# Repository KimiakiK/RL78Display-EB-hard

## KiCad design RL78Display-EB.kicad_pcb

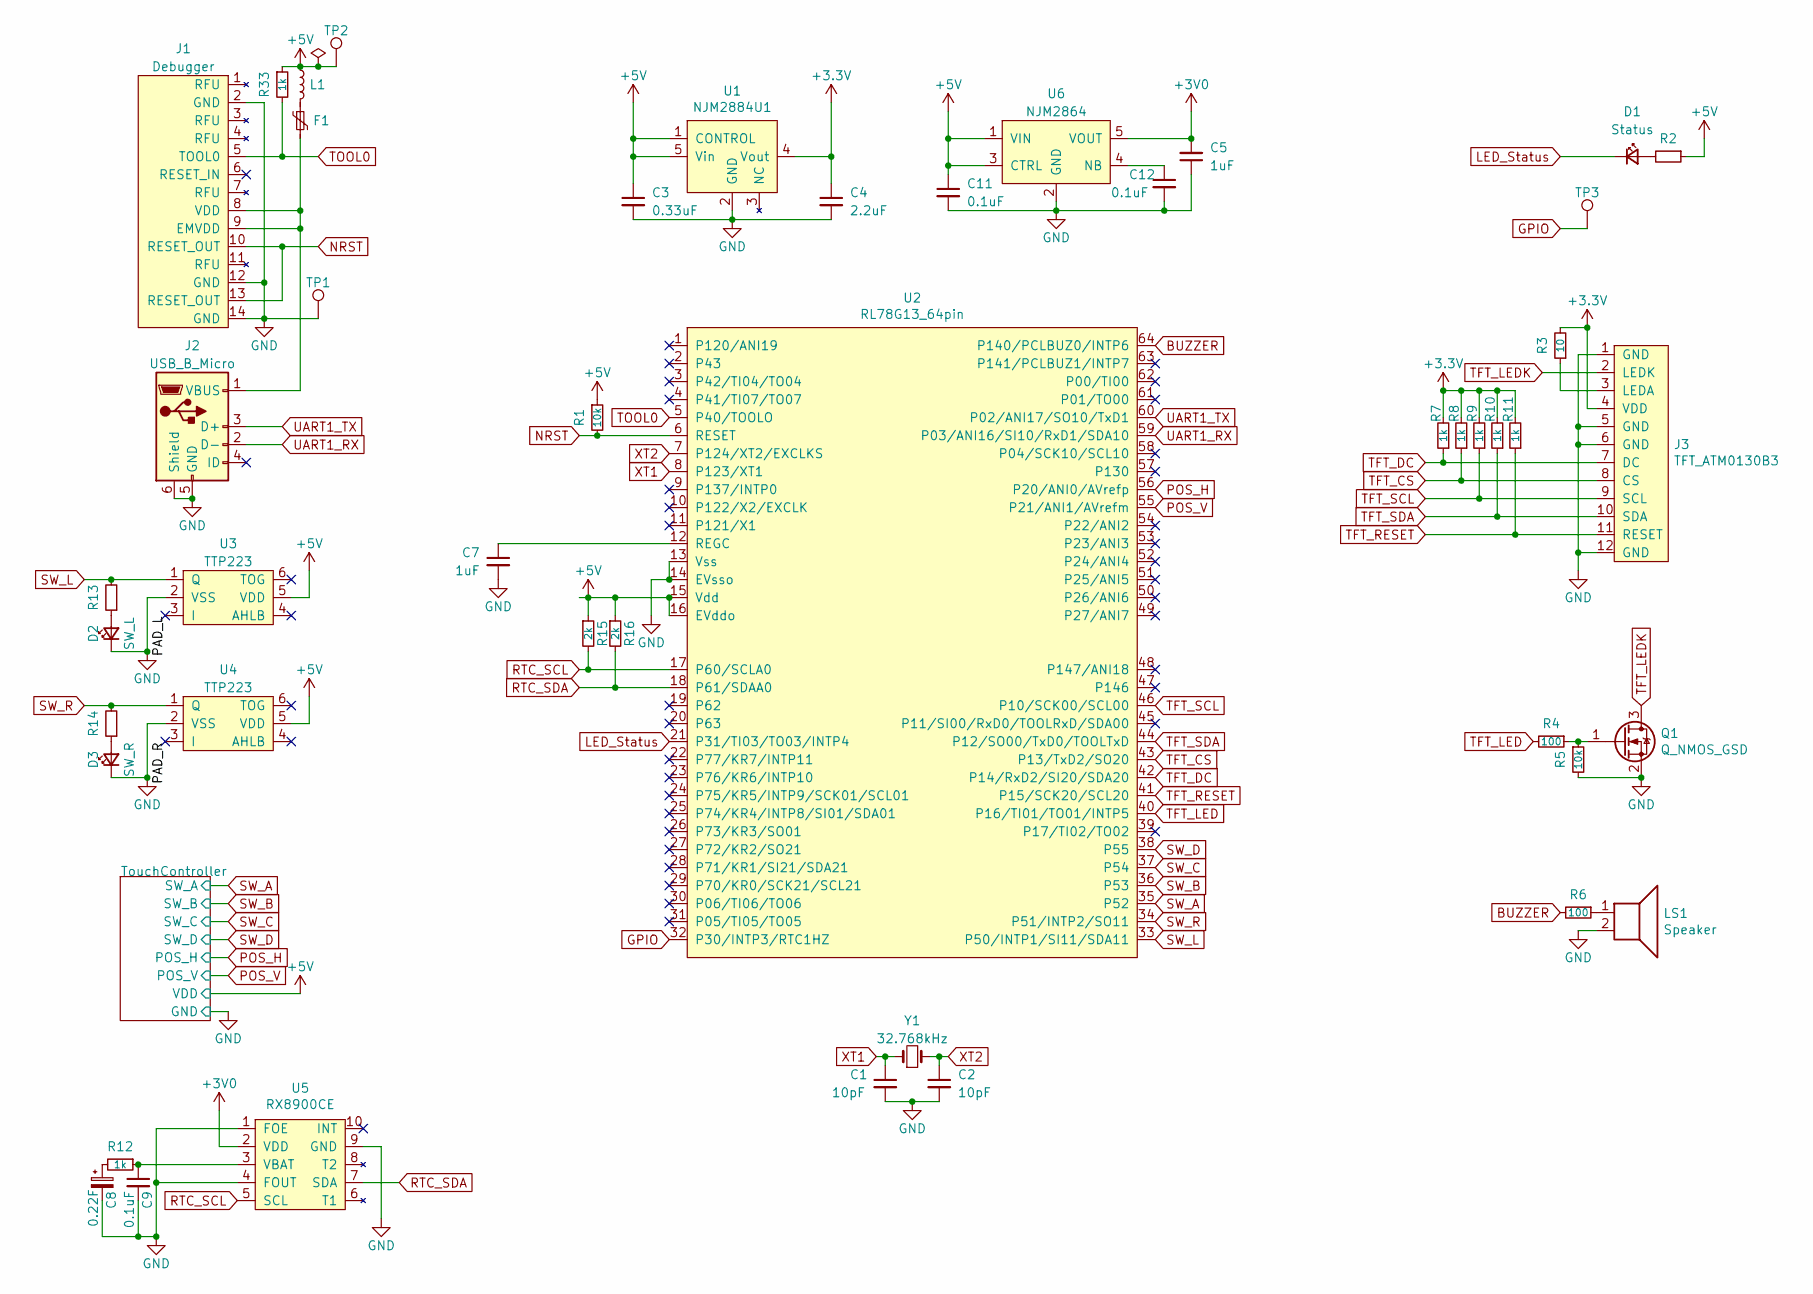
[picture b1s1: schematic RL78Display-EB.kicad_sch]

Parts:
C1, C2: 10pF; 1005Metric
C3: 0.33uF; 1608Metric
C4: 2.2uF; 1608Metric
C5, C7: 1uF; 1608Metric
C8: 0.22F; DCK-3R3E224-E
C9, C11, C12: 0.1uF; 1608Metric
D1: Status; 1608Metric
D2: SW_L; 1608Metric
D3: SW_R; 1608Metric
F1: Polyfuse_Small; 1608Metric
J1: Debugger; IDC-Header_2x07_P2.54mm_Vertical
J2: USB_B_Micro; UX60SC-MB-5ST
J3: TFT_ATM0130B3; Hirose_FH12-12S-0.5SH_1x12-1MP_P0.50mm_Horizontal
L1: L_Small; 1608Metric
LS1: Speaker; PKMCS0909E4000
Q1: Q_NMOS_GSD; SOT-23
R1, R5: 10k; 1608Metric
R2, R13, R14: R; 1608Metric
R3: 10; 1608Metric
R4, R6: 100; 1608Metric
R7, R8, R9, R10, R11, R12, R33: 1k; 1608Metric
R15, R16: 2k; 1608Metric
TP1, TP2, TP3: TestPoint; TestPoint_THTPad_D1.4mm_Drill0.8mm
U1: NJM2884U1; SOT-89-5
U2: RL78G13_64pin; LQFP-64-12x12mm-P0.65mm_FusionPCB_TP
U3, U4: TTP223; SOT-23-6
U5: RX8900CE
U6: NJM2864; SOT-23-5
Y1: 32.768kHz; Crystal_SMD_3215-2Pin

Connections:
+3.3V: C4.1, J3.4 (VDD), R3.2, R7.2, R8.2, R9.2, R10.2, R11.2, U1.4 (Vout)
+3V0: C5.2, U5.2 (VDD), U6.5 (VOUT)
+5V: C3.1, C11.1, L1.1, R1.1, R2.1, R15.1, R16.1, R33.1, TP2.1, U1.1 (CONTROL), U1.5 (Vin), U2.15 (Vdd), U2.16 (EVddo), U3.5 (VDD), U4.5 (VDD), U6.1 (VIN), U6.3 (CTRL); also elsewhere on the board
/PAD_L: U3.3 (I)
/PAD_R: U4.3 (I)
BUZZER: R6.2, U2.64 (P140/PCLBUZ0/INTP6)
GND: C1.2, C2.2, C3.2, C4.2, C5.1, C7.2, C8.2, C9.2, C11.2, C12.2, D2.1 (K), D3.1 (K), J1.2 (GND), J1.12 (GND), J1.14 (GND), J2.5 (GND), J2.6 (Shield), J3.1 (GND), J3.5 (GND), J3.6 (GND), J3.12 (GND), LS1.2, Q1.2 (S), R5.2, TP1.1, U1.2 (GND), U2.13 (Vss), U2.14 (EVsso), U3.2 (VSS), U4.2 (VSS), U5.1 (FOE), U5.4 (FOUT), U5.9 (GND), U6.2 (GND); also elsewhere on the board
GPIO: TP3.1, U2.32 (P30/INTP3/RTC1HZ)
LED_Status: D1.1 (K), U2.21 (P31/TI03/TO03/INTP4)
NRST: J1.10 (RESET_OUT), J1.13 (RESET_OUT), R1.2, U2.6 (RESET)
unnamed: C7.1, U2.12 (REGC)
unnamed: C8.1, R12.2
unnamed: C9.1, R12.1, U5.3 (VBAT)
unnamed: C12.1, U6.4 (NB)
unnamed: D1.2 (A), R2.2
unnamed: D2.2 (A), R13.1
unnamed: D3.2 (A), R14.1
unnamed: F1.1, L1.2
unnamed: F1.2, J1.8 (VDD), J1.9 (EMVDD), J2.1 (VBUS)
unnamed: J3.3 (LEDA), R3.1
unnamed: LS1.1, R6.1
unnamed: Q1.1 (G), R4.1, R5.1
POS_H: U2.56 (P20/ANI0/AVrefp); also elsewhere on the board
POS_V: U2.55 (P21/ANI1/AVrefm); also elsewhere on the board
RTC_SCL: R15.2, U2.17 (P60/SCLA0), U5.5 (SCL)
RTC_SDA: R16.2, U2.18 (P61/SDAA0), U5.7 (SDA)
SW_A: U2.35 (P52); also elsewhere on the board
SW_B: U2.36 (P53); also elsewhere on the board
SW_C: U2.37 (P54); also elsewhere on the board
SW_D: U2.38 (P55); also elsewhere on the board
SW_L: R13.2, U2.33 (P50/INTP1/SI11/SDA11), U3.1 (Q)
SW_R: R14.2, U2.34 (P51/INTP2/SO11), U4.1 (Q)
TFT_CS: J3.8 (CS), R8.1, U2.43 (P13/TxD2/SO20)
TFT_DC: J3.7 (DC), R7.1, U2.42 (P14/RxD2/SI20/SDA20)
TFT_LED: R4.2, U2.40 (P16/TI01/TO01/INTP5)
TFT_LEDK: J3.2 (LEDK), Q1.3 (D)
TFT_RESET: J3.11 (RESET), R11.1, U2.41 (P15/SCK20/SCL20)
TFT_SCL: J3.9 (SCL), R9.1, U2.46 (P10/SCK00/SCL00)
TFT_SDA: J3.10 (SDA), R10.1, U2.44 (P12/SO00/TxD0/TOOLTxD)
TOOL0: J1.5 (TOOL0), R33.2, U2.5 (P40/TOOLO)
UART1_RX: J2.2 (D-), U2.59 (P03/ANI16/SI10/RxD1/SDA10)
UART1_TX: J2.3 (D+), U2.60 (P02/ANI17/SO10/TxD1)
XT1: C1.1, U2.8 (P123/XT1), Y1.1
XT2: C2.1, U2.7 (P124/XT2/EXCLKS), Y1.2

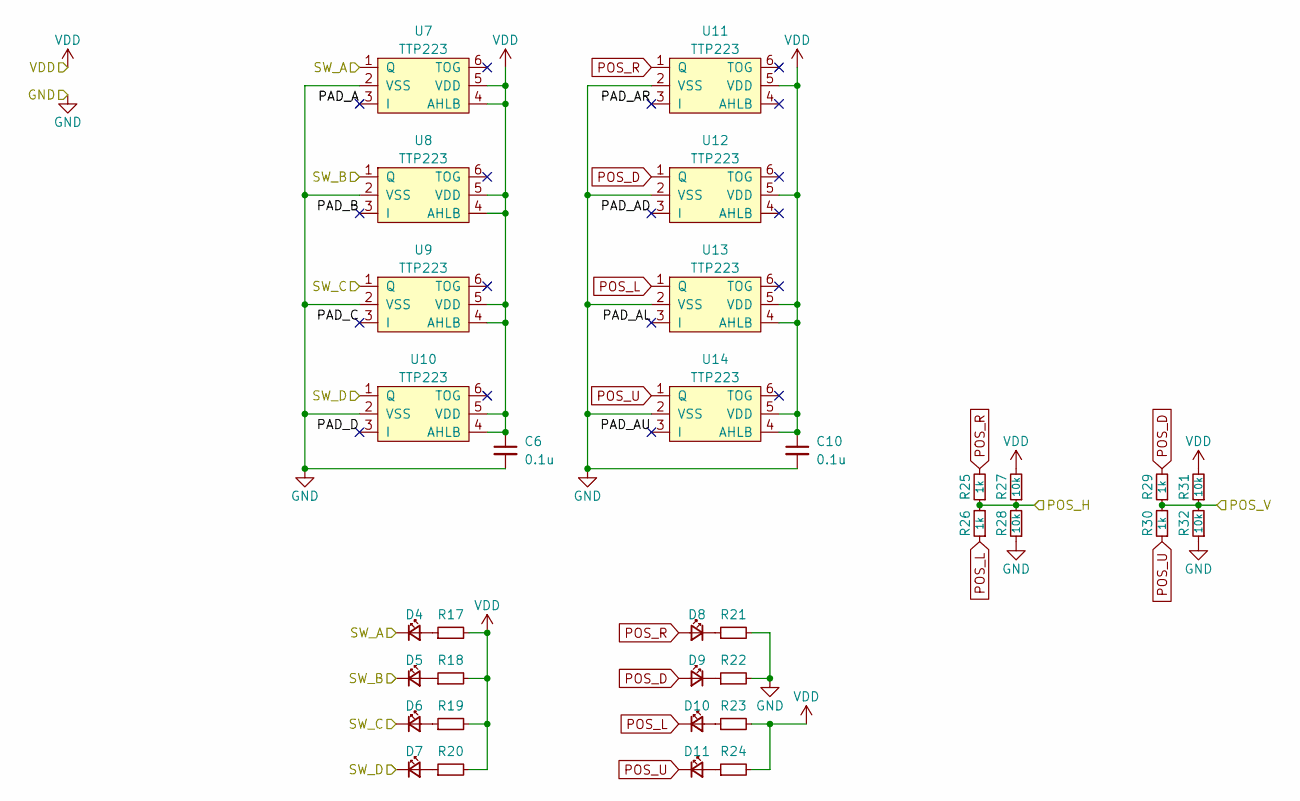
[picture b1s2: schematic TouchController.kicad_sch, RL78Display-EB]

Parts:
C6, C10: 0.1u; 1608Metric
D4, D5, D6, D7, D8, D9, D10, D11: LED; 1608Metric
R17, R18, R19, R20, R21, R22, R23, R24: R; 1608Metric
R25, R26, R29, R30: 1k; 1608Metric
R27, R28, R31, R32: 10k; 1608Metric
U7, U8, U9, U10, U11, U12, U13, U14: TTP223; SOT-23-6

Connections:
+5V: C6.1, C10.1, R17.2, R18.2, R19.2, R20.2, R23.2, R24.2, R27.2, R31.2, U7.4 (AHLB), U7.5 (VDD), U8.4 (AHLB), U8.5 (VDD), U9.4 (AHLB), U9.5 (VDD), U10.4 (AHLB), U10.5 (VDD), U11.5 (VDD), U12.5 (VDD), U13.4 (AHLB), U13.5 (VDD), U14.4 (AHLB), U14.5 (VDD); also elsewhere on the board
/TouchController/PAD_A: U7.3 (I)
/TouchController/PAD_AD: U12.3 (I)
/TouchController/PAD_AL: U13.3 (I)
/TouchController/PAD_AR: U11.3 (I)
/TouchController/PAD_AU: U14.3 (I)
/TouchController/PAD_B: U8.3 (I)
/TouchController/PAD_C: U9.3 (I)
/TouchController/PAD_D: U10.3 (I)
GND: C6.2, C10.2, R21.2, R22.2, R28.1, R32.1, U7.2 (VSS), U8.2 (VSS), U9.2 (VSS), U10.2 (VSS), U11.2 (VSS), U12.2 (VSS), U13.2 (VSS), U14.2 (VSS); also elsewhere on the board
unnamed: D4.2 (A), R17.1
unnamed: D5.2 (A), R18.1
unnamed: D6.2 (A), R19.1
unnamed: D7.2 (A), R20.1
unnamed: D8.1 (K), R21.1
unnamed: D9.1 (K), R22.1
unnamed: D10.2 (A), R23.1
unnamed: D11.2 (A), R24.1
POS_D: D9.2 (A), R29.2, U12.1 (Q)
POS_H: R25.1, R26.2, R27.1, R28.2; also elsewhere on the board
POS_L: D10.1 (K), R26.1, U13.1 (Q)
POS_R: D8.2 (A), R25.2, U11.1 (Q)
POS_U: D11.1 (K), R30.1, U14.1 (Q)
POS_V: R29.1, R30.2, R31.1, R32.2; also elsewhere on the board
SW_A: D4.1 (K), U7.1 (Q); also elsewhere on the board
SW_B: D5.1 (K), U8.1 (Q); also elsewhere on the board
SW_C: D6.1 (K), U9.1 (Q); also elsewhere on the board
SW_D: D7.1 (K), U10.1 (Q); also elsewhere on the board

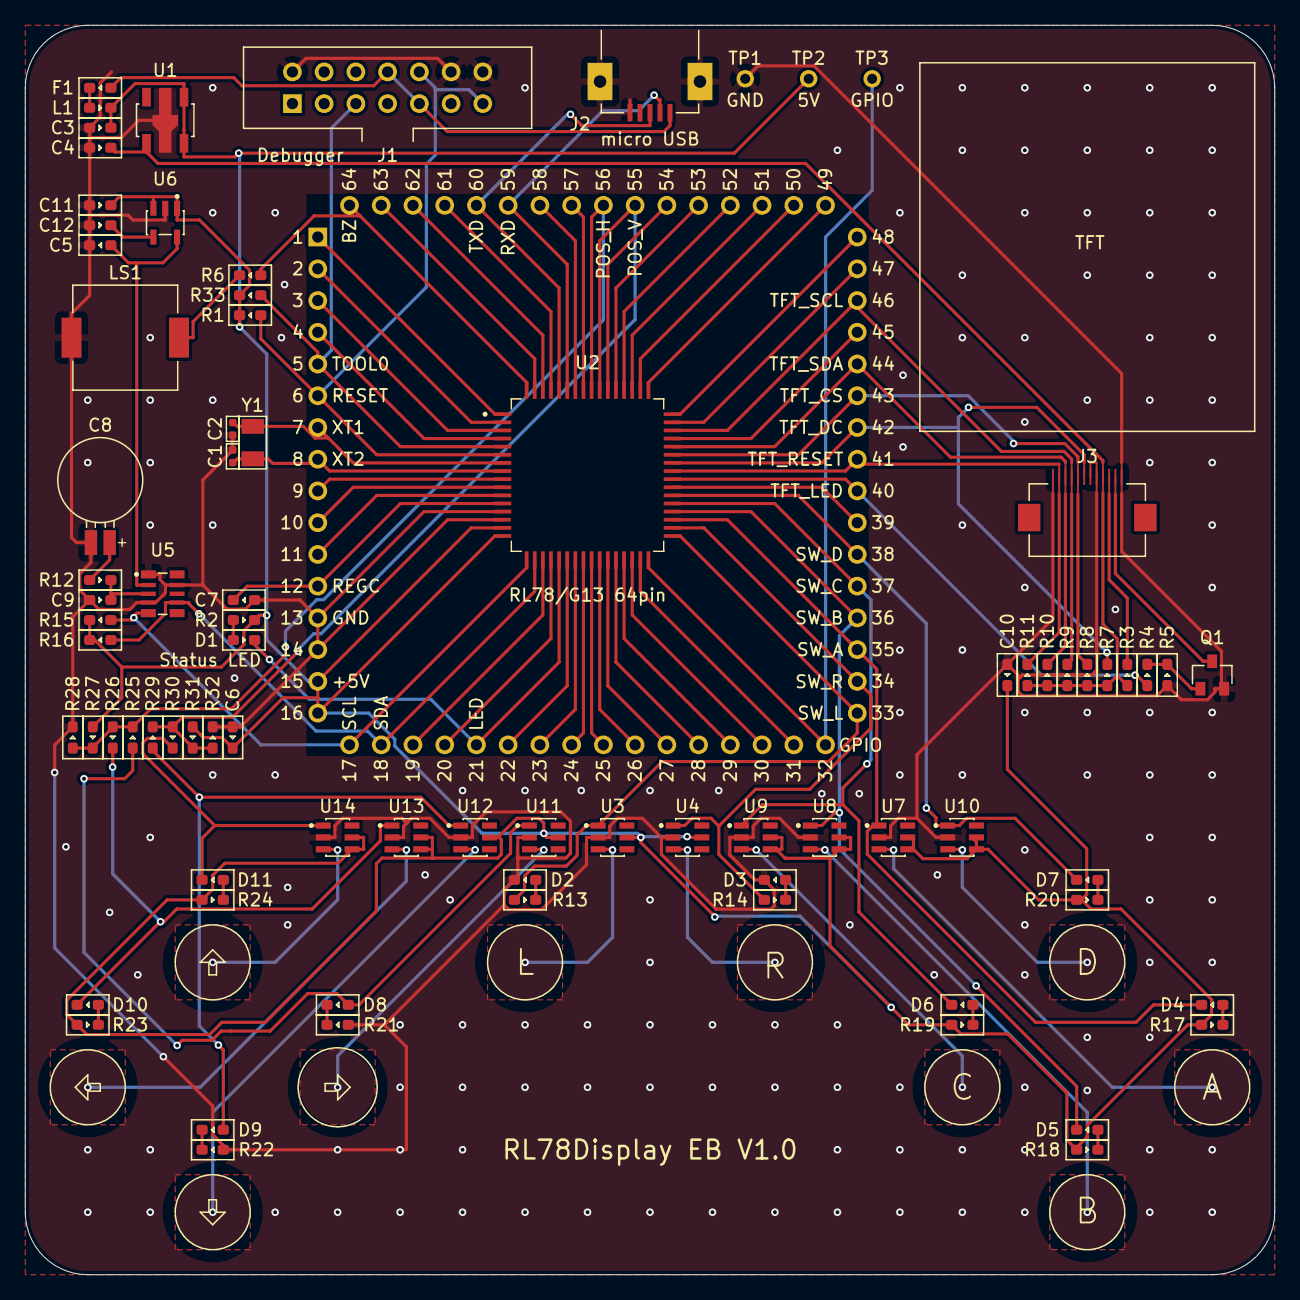
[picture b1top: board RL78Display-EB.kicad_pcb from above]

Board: 2 copper layers, 100.0 x 100.0 mm, 81 parts (0 on the bottom side), 54 nets.

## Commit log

2022-11-05 基板V1.0
